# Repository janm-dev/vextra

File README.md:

# Vextra - Vehicle Extras

Vextra is an extensible system of vehicle (car, bicycle, motorbike, etc.) extras, including position tracking, smart accessories, and more.

## Repository Structure

- `api` - Vextra data access / API server
- `db` - Vextra database interface (support for Timescale DB and a debugging/testing stub)
- `firmware` - Vextra Device firmware (for ESP32-C6)
- `hardware` - Vextra Device schematic, PCB, and additional hardware design
- `ingest` - Vextra data ingest server (over UDP and HTTPS)
- `proto` - Vextra protocols
- `web` - Vextra website front-end

## Licenses

Vextra software (`api`, `db`, `firmware`, `ingest`, `proto`, and `web`) is licensed under the GNU AGPL v3 or later ([`AGPL-3.0-or-later`](https://spdx.org/licenses/AGPL-3.0-or-later.html)).
You can find the full license text in the `LICENSE-AGPL` file.

Vextra hardware (`hardware`) is **partially** licensed under the CERN Open Hardware Licence - Strongly Reciprocal Version 2 or later ([`CERN-OHL-S-2.0+`](https://ohwr.org/cern_ohl_s_v2.txt)).
See `hardware/README.md` for details, and the `LICENSE-OHL` file for the full text of the CERN OHL.

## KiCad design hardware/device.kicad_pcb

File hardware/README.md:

# Vextra Device Hardware

Vextra hardware, including the device's schematic, PCB layout, and additional external hardware.

## Main Device Components

- MCU - ESP32-C6-WROOM-1(U)
- GNSS receiver - ST Teseo-VIC3DA or other pin-compatible modules (e.g. u-blox NEO series)
- Mobile transceiver - Waveshare SimCom SIM7600 module
- Battery - Li-Ion / Li-Po
- Battery Charger - TP4054
- Power supply - TPS54260 and HE9073
- Antennas - 2 x L1 or L1/L5 GNSS, 2 x 4G/3G/2G cellular, 1 x 2.4 GHz WiFi/BLE

## Device PCB

The PCB is split into three sections with slots between them: the power supply on the left, the MCU/GNSS section in the middle, and the cellular section on the right.

These sections are designed to be reusable for other purposes, e.g. the power supply section can act as a USB power supply or Li-Ion/Li-Po battery charger when removed from the rest of the board.
As such, not all components need to be installed for full operation for a specific purpose, e.g. the LEDs when low power consumption is needed or Q5 and Q6 when the USB port is not used as a power source for other USB devices.

## Additional Hardware

A case with mounting hardware for the Vextra Device is available as STEP files in `case` or [on Onshape](https://cad.onshape.com/documents/913efcab07442fbc03a0e56f/).

## Licenses

The schematic(s) and PCB(s) (KiCad files in this directory) are licensed under the CERN Open Hardware Licence - Strongly Reciprocal Version 2 or later ([`CERN-OHL-S-2.0+`](https://ohwr.org/cern_ohl_s_v2.txt)).

Additional external hardware (STEP files and associated documentation in subdirectories of this directory; e.g. the device's case and mounting hardware) are made available under the confusing and *iiuc* self-contradictory Onshape Free license (<https://www.onshape.com/en/legal/terms-of-use>, quoted below).
Commercial use might be - but probably isn't - allowed; use at your own risk and ask a lawyer.

> Onshape Free is a fully featured CAD and PDM platform perfect for **open-source** projects, makers, hobbyists and those learning to use modern CAD. This no-cost plan is meant for creating **non-commercial** product designs that are **open-source** publicly online.

*From <https://www.onshape.com/en/products/free> with added emphasis*

> \[...\] Customer grants a worldwide, royaltyfree and non-exclusive license to any End User or third party accessing the Public Document to use the intellectual property contained in Customer's Public Document without restriction, including without limitation the rights to use, copy, modify, merge, publish, distribute, sublicense, and/or sell copies of the Document, and to permit persons to whom the Document is made available to do the same.
> \[...\]
> Free versions of the Service are intended to support (a) creating and editing intellectual property for non-commercial purposes \[...\]

*From <https://www.onshape.com/en/legal/terms-of-use>*

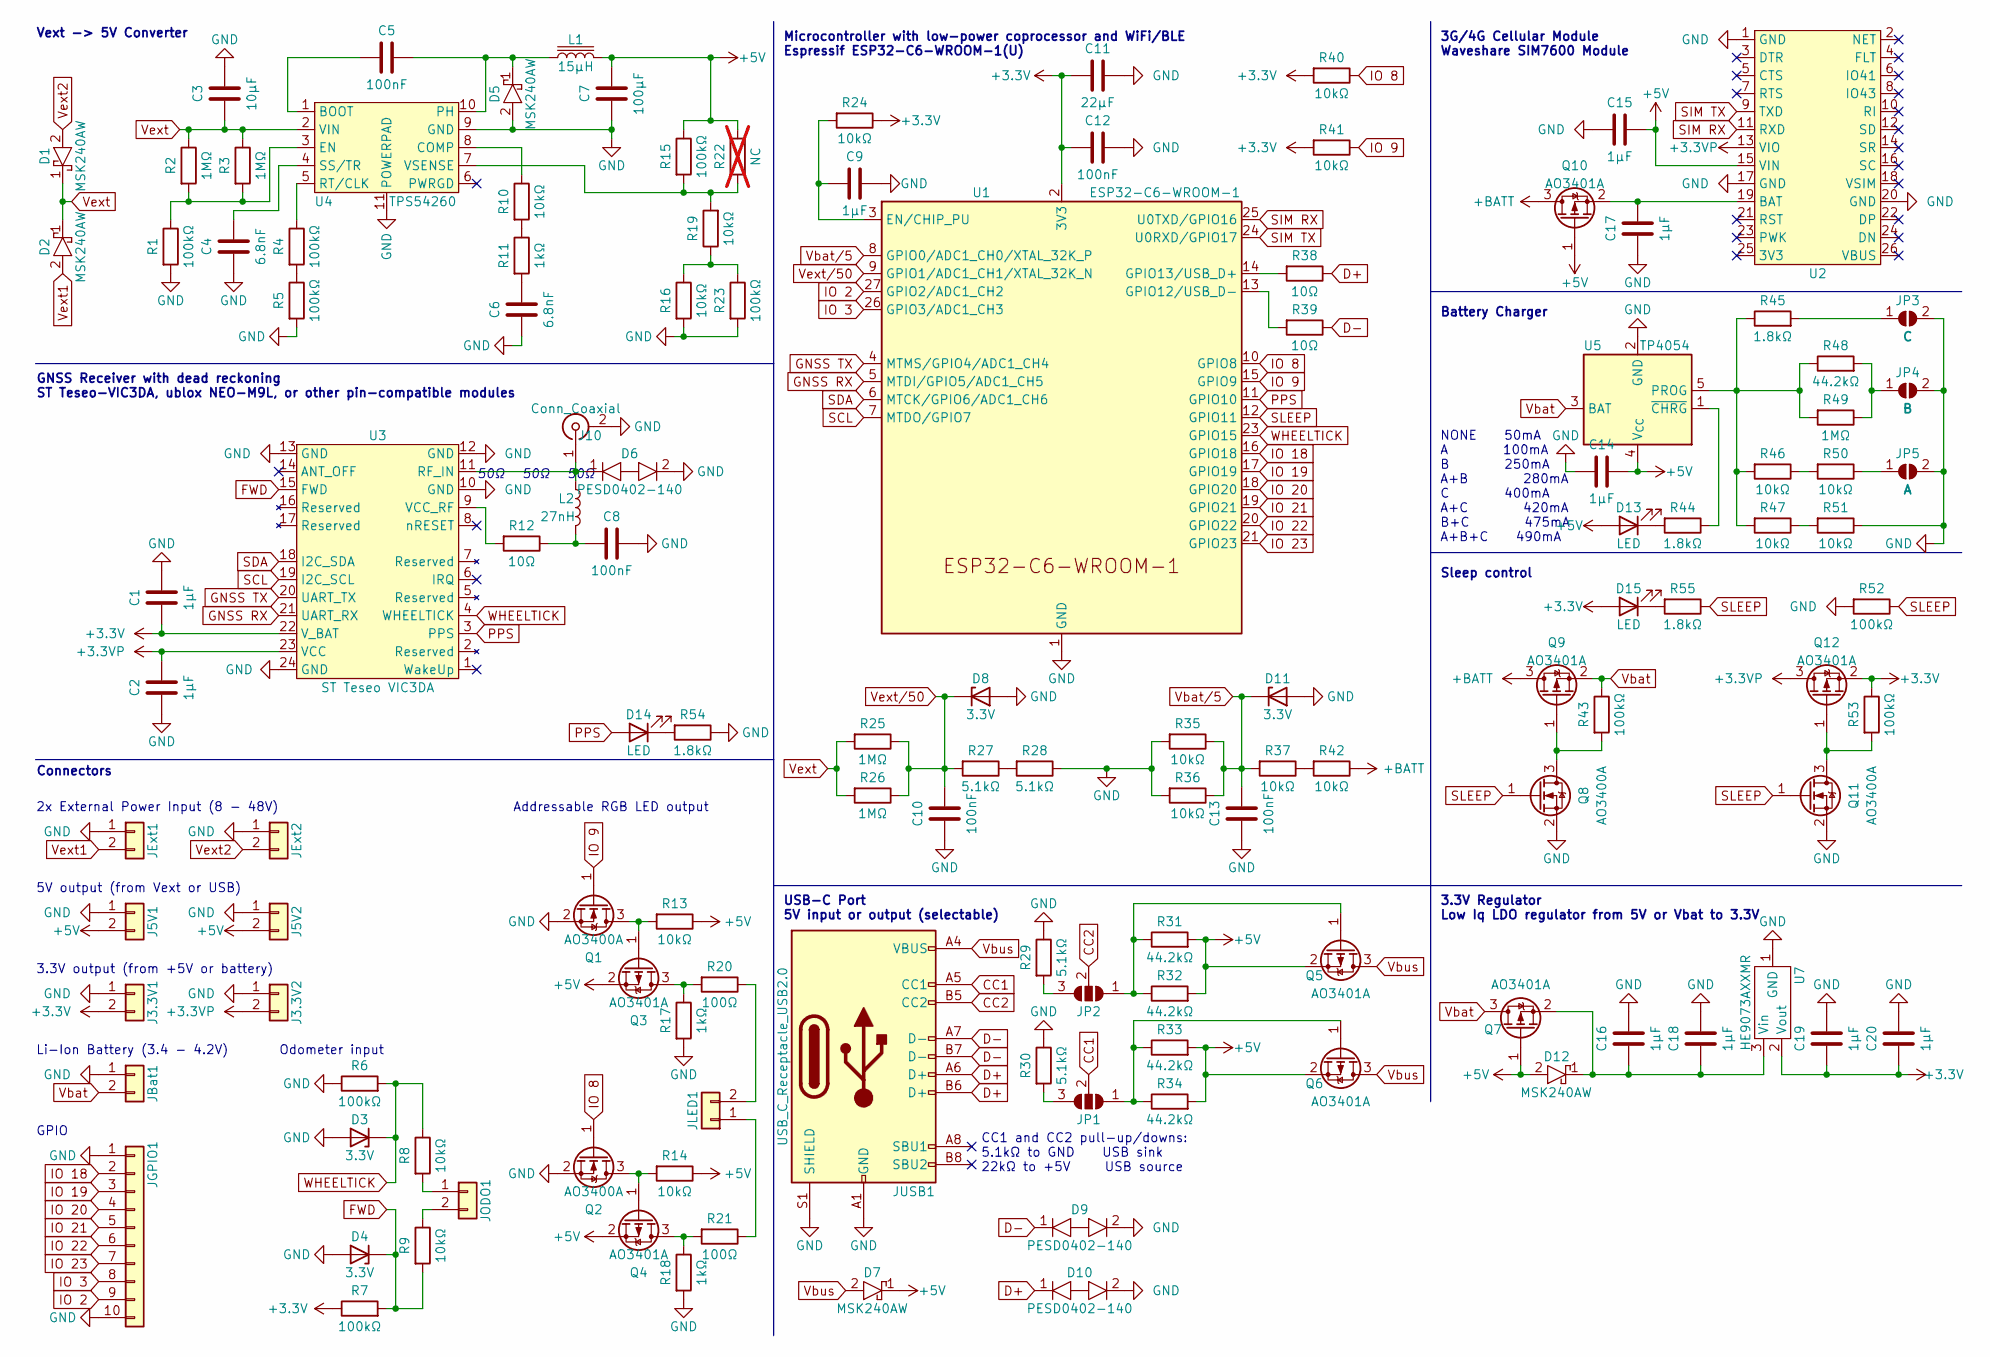
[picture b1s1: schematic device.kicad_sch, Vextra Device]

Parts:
C1, C2, C9, C14, C15, C16, C17, C18, C19, C20: 1µF; C_0603_1608Metric
C3: 10µF; C_0805_2012Metric
C4, C6: 6.8nF; C_0603_1608Metric
C5, C8, C10, C12, C13: 100nF; C_0603_1608Metric
C7: 100µF; C_1206_3216Metric
C11: 22µF; C_0603_1608Metric
D1, D2, D5, D7, D12: MSK240AW
D3, D4, D8, D11: 3.3V; SMAF
D6, D9, D10: PESD0402-140; D_0402_1005Metric
D13, D14, D15: LED; LED_0603_1608Metric
J3.3V1, J5V1: Conn_01x02; PinHeader_1x02_P2.54mm_Vertical
J3.3V2, J5V2: Conn_01x02; PH-2AWD
J10: Conn_Coaxial; U.FL_Hirose_U.FL-R-SMT-1_Vertical
JBat1: Conn_01x02; PH-2AWD
JExt1, JExt2: Conn_01x02; PH-2AWD
JGPIO1: Conn_01x10; PinHeader_1x10_P2.54mm_Vertical
JLED1: Conn_01x02; PH-2AWD
JODO1: Conn_01x02; PH-2AWD
JP1, JP2: SolderJumper_3_Open; SolderJumper-3_P1.3mm_Open_RoundedPad1.0x1.5mm
JP3: C; SolderJumper-2_P1.3mm_Open_RoundedPad1.0x1.5mm
JP4: B; SolderJumper-2_P1.3mm_Open_RoundedPad1.0x1.5mm
JP5: A; SolderJumper-2_P1.3mm_Open_RoundedPad1.0x1.5mm
JUSB1: USB_C_Receptacle_USB2.0; USB_C_Receptacle_HRO_TYPE-C-31-M-12
L1: 15µH; Inductor SMD 11.6x10.1
L2: 27nH; L_0603_1608Metric
Q1, Q2, Q8, Q11: AO3400A; SOT-23
Q3, Q4, Q5, Q6, Q7, Q9, Q10, Q12: AO3401A; SOT-23
R1, R4, R5, R6, R7, R15, R23, R43, R52, R53: 100kΩ; R_0603_1608Metric
R2, R3, R25, R26, R49: 1MΩ; R_0603_1608Metric
R8, R9, R10, R13, R14, R16, R19, R24, R35, R36, R37, R40, R41, R42, R46, R47, R50, R51: 10kΩ; R_0603_1608Metric
R11, R17, R18: 1kΩ; R_0603_1608Metric
R12, R38, R39: 10Ω; R_0603_1608Metric
R20, R21: 100Ω; R_0603_1608Metric
R22: NC; R_0603_1608Metric; not fitted
R27, R28, R29, R30: 5.1kΩ; R_0603_1608Metric
R31, R32, R33, R34, R48: 44.2kΩ; R_0603_1608Metric
R44, R45, R54, R55: 1.8kΩ; R_0603_1608Metric
U1: ESP32-C6-WROOM-1; ESP32-C6-WROOM-1U
U2: Waveshare SIM7600G-H Module THT
U3: ST Teseo VIC3DA
U4: TPS54260; TPS54260DGQR
U5: TP4054; TSOT-23-5
U7: HE9073AXXMR; SOT-23

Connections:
+3.3V: C1.1, C11.1, C12.1, C19.1, C20.1, D15.2 (A), J3.3V1.2, Q12.2 (S), R7.1, R24.1, R40.2, R41.2, R53.1, U1.2 (3V3), U3.22 (V_BAT), U7.2 (Vout)
+3.3VP: C2.2, J3.3V2.2, Q12.3 (D), U2.13 (VIO), U3.23 (VCC)
+5V: C7.2, C14.2, C15.2, D7.1, D12.2, D13.2 (A), J5V1.2, J5V2.2, L1.2, Q3.2 (S), Q4.2 (S), Q5.2 (S), Q6.2 (S), Q7.1 (G), Q10.1 (G), R13.1, R14.1, R15.1, R22.1, R31.2, R32.2, R33.2, R34.2, U2.15 (VIN), U5.4 (V_{CC})
+BATT: Q9.3 (D), Q10.3 (D), R42.1
CC1: JP1.2 (C), JUSB1.A5 (CC1)
CC2: JP2.2 (C), JUSB1.B5 (CC2)
D+: D10.1, JUSB1.A6 (D+), JUSB1.B6 (D+), R38.1
D-: D9.1, JUSB1.A7 (D-), JUSB1.B7 (D-), R39.1
FWD: D4.1 (K), R7.2, R9.2, U3.15 (FWD)
GND: C1.2, C2.1, C3.2, C4.1, C6.1, C7.1, C8.2, C9.2, C10.1, C11.2, C12.2, C13.1, C14.1, C15.1, C16.1, C17.1, C18.1, C19.2, C20.2, D3.2 (A), D4.2 (A), D5.2, D6.2, D8.2 (A), D9.2, D10.2, D11.2 (A), J3.3V1.1, J3.3V2.1, J5V1.1, J5V2.1, J10.2 (Ext), JBat1.1, JExt1.1, JExt2.1, JGPIO1.1, JGPIO1.10, JP3.2 (B), JP4.2 (B), JP5.2 (B), JUSB1.A1 (GND), JUSB1.A12 (GND), JUSB1.B1 (GND), JUSB1.B12 (GND), JUSB1.S1 (SHIELD), Q1.2 (S), Q2.2 (S), Q8.2 (S), Q11.2 (S), R1.2, R5.2, R6.1, R16.2, R17.2, R18.2, R23.2, R28.1, R29.1, R30.1, R35.2, R36.2, R51.1, R52.2, R54.1, U1.1 (GND), U1.28 (GND), U1.29 (GND), U2.1 (GND), U2.17 (GND), U2.20 (GND), U3.10 (GND), U3.12 (GND), U3.13 (GND), U3.24 (GND), U4.9 (GND), U4.11 (POWERPAD), U5.2 (GND), U7.1 (GND)
GNSS RX: U1.5 (MTDI/GPIO5/ADC1_CH5), U3.21 (UART_RX)
GNSS TX: U1.4 (MTMS/GPIO4/ADC1_CH4), U3.20 (UART_TX)
IO 2: JGPIO1.9, U1.27 (GPIO2/ADC1_CH2)
IO 3: JGPIO1.8, U1.26 (GPIO3/ADC1_CH3)
IO 8: Q2.1 (G), R40.1, U1.10 (GPIO8)
IO 9: Q1.1 (G), R41.1, U1.15 (GPIO9)
IO 18: JGPIO1.2, U1.16 (GPIO18)
IO 19: JGPIO1.3, U1.17 (GPIO19)
IO 20: JGPIO1.4, U1.18 (GPIO20)
IO 21: JGPIO1.5, U1.19 (GPIO21)
IO 22: JGPIO1.6, U1.20 (GPIO22)
IO 23: JGPIO1.7, U1.21 (GPIO23)
unnamed: C6.2, R11.2
unnamed: C8.1, L2.2, R12.1
unnamed: D13.1 (K), R44.2
unnamed: D14.1 (K), R54.2
unnamed: D15.1 (K), R55.2
unnamed: D6.1, J10.1 (In), L2.1, U3.11 (RF_IN)
unnamed: JLED1.1, R21.1
unnamed: JLED1.2, R20.1
unnamed: JODO1.1, R8.2
unnamed: JODO1.2, R9.1
unnamed: JP1.1 (A), Q6.1 (G), R33.1, R34.1
unnamed: JP1.3 (B), R30.2
unnamed: JP2.1 (A), Q5.1 (G), R31.1, R32.1
unnamed: JP2.3 (B), R29.2
unnamed: JP3.1 (A), R45.2
unnamed: JP4.1 (A), R48.2, R49.1
unnamed: JP5.1 (A), R50.1
unnamed: Q1.3 (D), Q3.1 (G), R13.2
unnamed: Q2.3 (D), Q4.1 (G), R14.2
unnamed: Q3.3 (D), R17.1, R20.2
unnamed: Q4.3 (D), R18.1, R21.2
unnamed: C16.2, C18.2, D12.1, Q7.2 (S), U7.3 (Vin)
unnamed: Q8.3 (D), Q9.1 (G), R43.2
unnamed: C17.2, Q10.2 (S), U2.19 (BAT)
unnamed: Q11.3 (D), Q12.1 (G), R53.2
unnamed: R4.2, R5.1
unnamed: R10.2, R11.1
unnamed: R16.1, R19.1, R23.1
unnamed: R27.1, R28.2
unnamed: R37.1, R42.2
unnamed: R46.1, R50.2
unnamed: R47.1, R51.2
unnamed: C9.1, R24.2, U1.3 (EN/CHIP_PU)
unnamed: R39.2, U1.13 (GPIO12/USB_D-)
unnamed: R38.2, U1.14 (GPIO13/USB_D+)
unnamed: R12.2, U3.9 (VCC_RF)
unnamed: C5.1, U4.1 (BOOT)
unnamed: R10.1, U4.8 (COMP)
unnamed: R1.1, R2.2, R3.2, U4.3 (EN)
unnamed: C5.2, D5.1, L1.1, U4.10 (PH)
unnamed: R4.1, U4.5 (RT/CLK)
unnamed: C4.2, U4.4 (SS/TR)
unnamed: R15.2, R19.2, R22.2, U4.7 (VSENSE)
unnamed: R45.1, R46.2, R47.2, R48.1, R49.2, U5.5 (PROG)
unnamed: R44.1, U5.1 (~CHRG)
PPS: D14.2 (A), U1.11 (GPIO10), U3.3 (PPS)
SCL: U1.7 (MTDO/GPIO7), U3.19 (I2C_SCL)
SDA: U1.6 (MTCK/GPIO6/ADC1_CH6), U3.18 (I2C_SDA)
SIM RX: U1.25 (U0TXD/GPIO16), U2.11 (RXD)
SIM TX: U1.24 (U0RXD/GPIO17), U2.9 (TXD)
SLEEP: Q8.1 (G), Q11.1 (G), R52.1, R55.1, U1.12 (GPIO11)
Vbat: JBat1.2, Q7.3 (D), Q9.2 (S), R43.1, U5.3 (BAT)
Vbat/5: C13.2, D11.1 (K), R35.1, R36.1, R37.2, U1.8 (GPIO0/ADC1_CH0/XTAL_32K_P)
Vbus: D7.2, JUSB1.A4 (VBUS), JUSB1.A9 (VBUS), JUSB1.B4 (VBUS), JUSB1.B9 (VBUS), Q5.3 (D), Q6.3 (D)
Vext: C3.1, D1.1, D2.1, R2.1, R3.1, R25.2, R26.2, U4.2 (VIN)
Vext1: D2.2, JExt1.2
Vext2: D1.2, JExt2.2
Vext/50: C10.2, D8.1 (K), R25.1, R26.1, R27.2, U1.9 (GPIO1/ADC1_CH1/XTAL_32K_N)
WHEELTICK: D3.1 (K), R6.2, R8.1, U1.23 (GPIO15), U3.4 (WHEELTICK)

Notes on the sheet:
2x External Power Input (8 - 48V)
Battery Charger
50Ω
NONE 50mA A 100mA B 250mA A+B 280mA C 400mA A+C 420mA B+C 475mA A+B+C 490mA
3.3V Regulator Low Iq LDO regulator from 5V or Vbat to 3.3V
3.3V output (from +5V or battery)
5V output (from Vext or USB)
Sleep control
GNSS Receiver with dead reckoning ST Teseo-VIC3DA, ublox NEO-M9L, or other pin-compatible modules
Addressable RGB LED output
GPIO
Vext -> 5V Converter
Connectors
CC1 and CC2 pull-up/downs: 5.1kΩ to GND USB sink 22kΩ to +5V USB source
Microcontroller with low-power coprocessor and WiFi/BLE Espressif ESP32-C6-WROOM-1(U)
USB-C Port 5V input or output (selectable)
Li-Ion Battery (3.4 - 4.2V)
Odometer input
3G/4G Cellular Module Waveshare SIM7600 Module

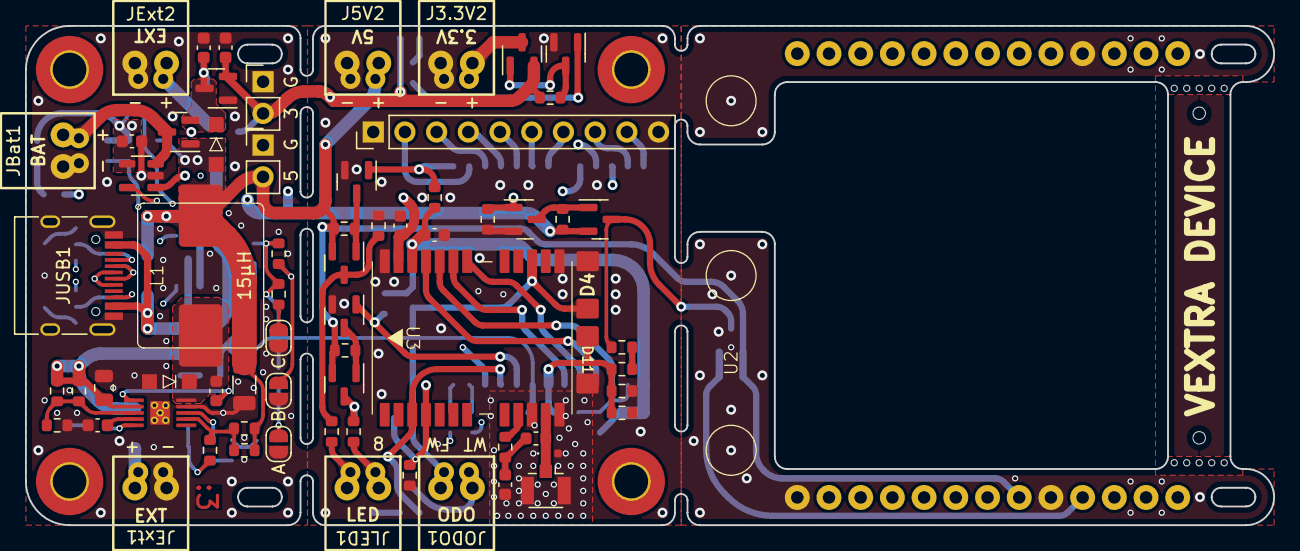
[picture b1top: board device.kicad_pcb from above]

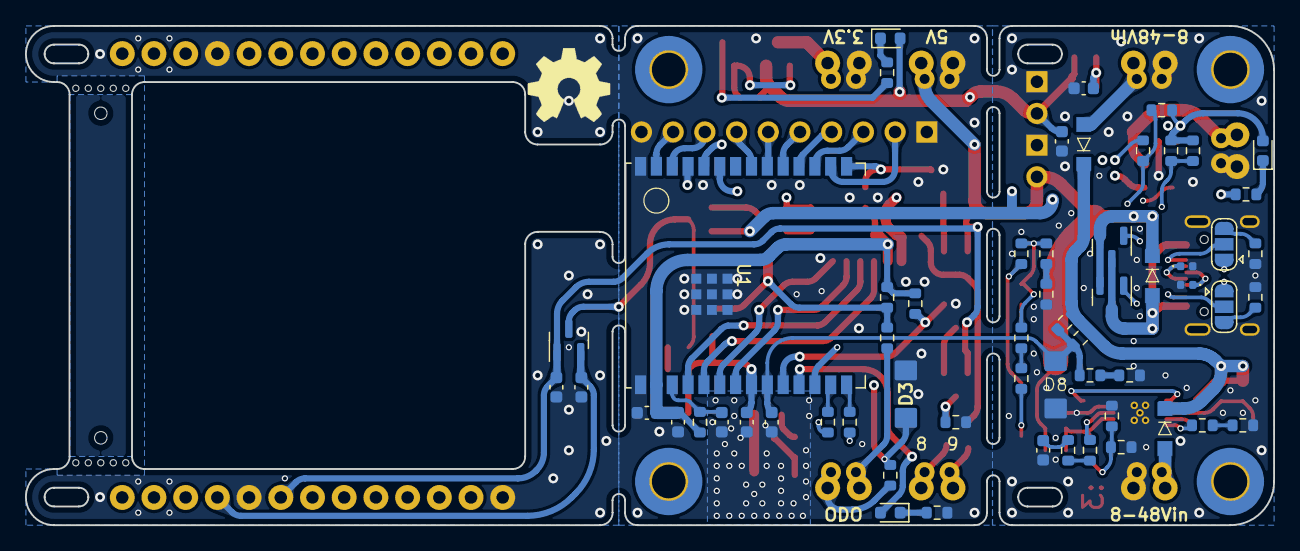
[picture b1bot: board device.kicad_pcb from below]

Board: 4 copper layers, 100.0 x 40.0 mm, 127 parts (58 on the bottom side), 81 nets.

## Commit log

2024-03-02 feat(hardware): add device schematics and pcb
2024-03-02 feat(hardware): add device case
2024-03-02 feat(hardware): add case mount
2024-03-05 feat(hardware): add case endcaps
2024-04-03 fix(hardware): fix 5V divider resistors
    oops, i forgot some parentheses when calculating them initially
